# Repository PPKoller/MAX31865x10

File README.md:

# MAX31865x10
PCB for serial 4-point measurement of ten PT-100 temperature sensors using Raspberry Pi.

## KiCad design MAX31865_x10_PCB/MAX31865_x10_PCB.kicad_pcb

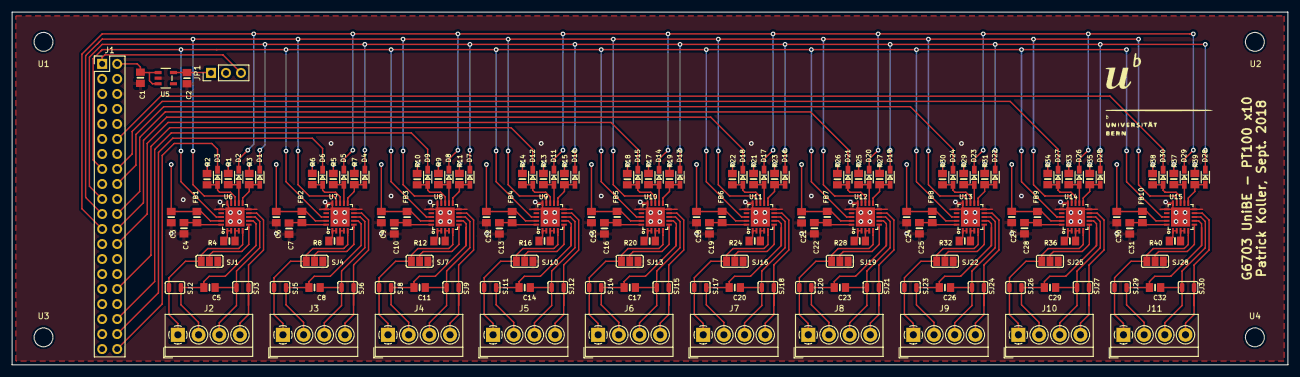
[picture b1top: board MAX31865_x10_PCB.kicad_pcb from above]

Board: 2 copper layers, 215.9 x 59.7 mm, 169 parts (0 on the bottom side), 128 nets.

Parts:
C1, C2: 10uF; 0805-NO
C3, C4, C6, C7, C9, C10, C12, C13, C15, C16, C18, C19, C21, C22, C24, C25, C27, C28, C30, C31: 0.1uF; 0805-NO
C5, C8, C11, C14, C17, C20, C23, C26, C29, C32: 100nF; 0805-NO
D1, D2, D3, D4, D5, D6, D7, D8, D9, D10, D11, D12, D13, D14, D15, D16, D17, D18, D19, D20, D21, D22, D23, D24, D25, D26, D27, D28, D29, D30: 1N4148; SOD-323
FB1, FB2, FB3, FB4, FB5, FB6, FB7, FB8, FB9, FB10: FERRITE-0805NO; 0805-NO
J1: Conn_02x20_Odd_Even; PinHeader_2x20_P2.54mm_Vertical
J2, J3, J4, J5, J6, J7, J8, J9, J10, J11: Conn_01x04; TerminalBlock_4Ucon_1x04_P3.50mm_Horizontal
JP1: Jumper_3_Bridged12; PinHeader_1x03_P2.54mm_Vertical
R1, R2, R3, R5, R6, R7, R9, R10, R11, R13, R14, R15, R17, R18, R19, R21, R22, R23, R25, R26, R27, R29, R30, R31, R33, R34, R35, R37, R38, R39: 10K; 0805-NO
R4, R8, R12, R16, R20, R24, R28, R32, R36, R40: 430Ω / 4300Ω 0.1%; 0805-NO
SJ1, SJ4, SJ7, SJ10, SJ13, SJ16, SJ19, SJ22, SJ25, SJ28: SOLDERJUMPER_2WAY; SOLDERJUMPER_2WAY_OPEN_NOPASTE
SJ2, SJ3, SJ5, SJ6, SJ8, SJ9, SJ11, SJ12, SJ14, SJ15, SJ17, SJ18, SJ20, SJ21, SJ23, SJ24, SJ26, SJ27, SJ29, SJ30: SOLDERJUMPER; SOLDERJUMPER_ARROW_NOPASTE
U1, U2, U3, U4: MOUNTINGHOLE3.0; MountingHole_3.2mm_M3
U5: MIC5225-3.3; SOT23-5
U6, U7, U8, U9, U10, U11, U12, U13, U14, U15: MAX31865; QFN20_4MM_0.65MM

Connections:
CLK_5V: D2.C, D5.C, D8.C, D11.C, D14.C, D17.C, D20.C, D23.C, D26.C, D29.C, J1.23
CS0_5V: D3.C, J1.40
CS1_5V: D6.C, J1.38
CS2_5V: D9.C, J1.36
CS3_5V: D12.C, J1.32
CS4_5V: D15.C, J1.26
CS5_5V: D18.C, J1.24
CS6_5V: D21.C, J1.22
CS7_5V: D24.C, J1.18
CS8_5V: D27.C, J1.16
CS9_5V: D30.C, J1.12
EXT_3V3: J1.1, JP1.3
EXT_5V: C1.1, J1.2, U5.1, U5.3
GND: C1.2, C2.2, C3.2, C4.2, C6.2, C7.2, C9.2, C10.2, C12.2, C13.2, C15.2, C16.2, C18.2, C19.2, C21.2, C22.2, C24.2, C25.2, C27.2, C28.2, C30.2, C31.2, J1.6, SJ1.1, SJ4.1, SJ7.1, SJ10.1, SJ13.1, SJ16.1, SJ19.1, SJ22.1, SJ25.1, SJ28.1, U5.2, U6.10, U6.15, U6.16, U6.PAD, U7.10, U7.15, U7.16, U7.PAD, U8.10, U8.15, U8.16, U8.PAD, U9.10, U9.15, U9.16, U9.PAD, U10.10, U10.15, U10.16, U10.PAD, U11.10, U11.15, U11.16, U11.PAD, U12.10, U12.15, U12.16, U12.PAD, U13.10, U13.15, U13.16, U13.PAD, U14.10, U14.15, U14.16, U14.PAD, U15.10, U15.15, U15.16, U15.PAD
unnamed: C4.1, FB1.1, U6.20
unnamed: C5.1, J2.2, SJ2.1, U6.7
unnamed: C5.2, J2.3, SJ3.2, U6.8
unnamed: C7.1, FB2.1, U7.20
unnamed: C8.1, J3.2, SJ5.1, U7.7
unnamed: C8.2, J3.3, SJ6.2, U7.8
unnamed: C10.1, FB3.1, U8.20
unnamed: C11.1, J4.2, SJ8.1, U8.7
unnamed: C11.2, J4.3, SJ9.2, U8.8
unnamed: C13.1, FB4.1, U9.20
unnamed: C14.1, J5.2, SJ11.1, U9.7
unnamed: C14.2, J5.3, SJ12.2, U9.8
unnamed: C16.1, FB5.1, U10.20
unnamed: C17.1, J6.2, SJ14.1, U10.7
unnamed: C17.2, J6.3, SJ15.2, U10.8
unnamed: C19.1, FB6.1, U11.20
unnamed: C20.1, J7.2, SJ17.1, U11.7
unnamed: C20.2, J7.3, SJ18.2, U11.8
unnamed: C22.1, FB7.1, U12.20
unnamed: C23.1, J8.2, SJ20.1, U12.7
unnamed: C23.2, J8.3, SJ21.2, U12.8
unnamed: C25.1, FB8.1, U13.20
unnamed: C26.1, J9.2, SJ23.1, U13.7
unnamed: C26.2, J9.3, SJ24.2, U13.8
unnamed: C28.1, FB9.1, U14.20
unnamed: C29.1, J10.2, SJ26.1, U14.7
unnamed: C29.2, J10.3, SJ27.2, U14.8
unnamed: C31.1, FB10.1, U15.20
unnamed: C32.1, J11.2, SJ29.1, U15.7
unnamed: C32.2, J11.3, SJ30.2, U15.8
unnamed: D1.A, R3.1, U6.11
unnamed: D2.A, R1.1, U6.12
unnamed: D3.A, R2.1, U6.13
unnamed: D4.A, R7.1, U7.11
unnamed: D5.A, R5.1, U7.12
unnamed: D6.A, R6.1, U7.13
unnamed: D7.A, R11.1, U8.11
unnamed: D8.A, R9.1, U8.12
unnamed: D9.A, R10.1, U8.13
unnamed: D10.A, R15.1, U9.11
unnamed: D11.A, R13.1, U9.12
unnamed: D12.A, R14.1, U9.13
unnamed: D13.A, R19.1, U10.11
unnamed: D14.A, R17.1, U10.12
unnamed: D15.A, R18.1, U10.13
unnamed: D16.A, R23.1, U11.11
unnamed: D17.A, R21.1, U11.12
unnamed: D18.A, R22.1, U11.13
unnamed: D19.A, R27.1, U12.11
unnamed: D20.A, R25.1, U12.12
unnamed: D21.A, R26.1, U12.13
unnamed: D22.A, R31.1, U13.11
unnamed: D23.A, R29.1, U13.12
unnamed: D24.A, R30.1, U13.13
unnamed: D25.A, R35.1, U14.11
unnamed: D26.A, R33.1, U14.12
unnamed: D27.A, R34.1, U14.13
unnamed: D28.A, R39.1, U15.11
unnamed: D29.A, R37.1, U15.12
unnamed: D30.A, R38.1, U15.13
unnamed: J2.1, SJ1.3, SJ2.2, U6.5
unnamed: J2.4, SJ3.1, U6.9
unnamed: J3.1, SJ4.3, SJ5.2, U7.5
unnamed: J3.4, SJ6.1, U7.9
unnamed: J4.1, SJ7.3, SJ8.2, U8.5
unnamed: J4.4, SJ9.1, U8.9
unnamed: J5.1, SJ10.3, SJ11.2, U9.5
unnamed: J5.4, SJ12.1, U9.9
unnamed: J6.1, SJ13.3, SJ14.2, U10.5
unnamed: J6.4, SJ15.1, U10.9
unnamed: J7.1, SJ16.3, SJ17.2, U11.5
unnamed: J7.4, SJ18.1, U11.9
unnamed: J8.1, SJ19.3, SJ20.2, U12.5
unnamed: J8.4, SJ21.1, U12.9
unnamed: J9.1, SJ22.3, SJ23.2, U13.5
unnamed: J9.4, SJ24.1, U13.9
unnamed: J10.1, SJ25.3, SJ26.2, U14.5
unnamed: J10.4, SJ27.1, U14.9
unnamed: J11.1, SJ28.3, SJ29.2, U15.5
unnamed: J11.4, SJ30.1, U15.9
unnamed: R4.1, U6.3, U6.4
unnamed: R4.2, U6.1, U6.2
unnamed: R8.1, U7.3, U7.4
unnamed: R8.2, U7.1, U7.2
unnamed: R12.1, U8.3, U8.4
unnamed: R12.2, U8.1, U8.2
unnamed: R16.1, U9.3, U9.4
unnamed: R16.2, U9.1, U9.2
unnamed: R20.1, U10.3, U10.4
unnamed: R20.2, U10.1, U10.2
unnamed: R24.1, U11.3, U11.4
unnamed: R24.2, U11.1, U11.2
unnamed: R28.1, U12.3, U12.4
unnamed: R28.2, U12.1, U12.2
unnamed: R32.1, U13.3, U13.4
unnamed: R32.2, U13.1, U13.2
unnamed: R36.1, U14.3, U14.4
unnamed: R36.2, U14.1, U14.2
unnamed: R40.1, U15.3, U15.4
unnamed: R40.2, U15.1, U15.2
unnamed: SJ1.2, U6.6
unnamed: SJ4.2, U7.6
unnamed: SJ7.2, U8.6
unnamed: SJ10.2, U9.6
unnamed: SJ13.2, U10.6
unnamed: SJ16.2, U11.6
unnamed: SJ19.2, U12.6
unnamed: SJ22.2, U13.6
unnamed: SJ25.2, U14.6
unnamed: SJ28.2, U15.6
RDY: J1.15, U6.18, U7.18, U8.18, U9.18, U10.18, U11.18, U12.18, U13.18, U14.18, U15.18
SDI_5V: D1.C, D4.C, D7.C, D10.C, D13.C, D16.C, D19.C, D22.C, D25.C, D28.C, J1.19
SDO: J1.21, U6.14, U7.14, U8.14, U9.14, U10.14, U11.14, U12.14, U13.14, U14.14, U15.14
VDD: C2.1, C3.1, C6.1, C9.1, C12.1, C15.1, C18.1, C21.1, C24.1, C27.1, C30.1, FB1.2, FB2.2, FB3.2, FB4.2, FB5.2, FB6.2, FB7.2, FB8.2, FB9.2, FB10.2, JP1.1, JP1.2, R1.2, R2.2, R3.2, R5.2, R6.2, R7.2, R9.2, R10.2, R11.2, R13.2, R14.2, R15.2, R17.2, R18.2, R19.2, R21.2, R22.2, R23.2, R25.2, R26.2, R27.2, R29.2, R30.2, R31.2, R33.2, R34.2, R35.2, R37.2, R38.2, R39.2, U5.5, U6.19, U7.19, U8.19, U9.19, U10.19, U11.19, U12.19, U13.19, U14.19, U15.19

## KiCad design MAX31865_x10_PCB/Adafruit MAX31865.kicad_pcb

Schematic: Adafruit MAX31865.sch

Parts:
C1, C2: 0.1uF; 0805-NO
C3: 100nF; 0805-NO
C4, C5: 10uF; 0805-NO
D1, D2, D3: 1N4148; SOD-323
FB1: FERRITE-0805NO; 0805-NO
FID1, FID2: FIDUCIAL\"\"; FIDUCIAL_1MM
JP1: HEADER-1X870MIL; 1X08_ROUND_70
R1: 430Ω / 4300Ω 0.1%; 0805-NO
R6, R7, R8: 10K; 0805-NO
SJ1: SOLDERJUMPER_2WAY; SOLDERJUMPER_2WAY_OPEN_NOPASTE
SJ3, SJ4: SOLDERJUMPER; SOLDERJUMPER_ARROW_NOPASTE
U1: MAX31865; QFN20_4MM_0.65MM
U3: MIC5225-3.3; SOT23-5
U$18, U$19: MOUNTINGHOLE2.5; MOUNTINGHOLE_2.5_PLATED
X1, X2: 3.5mm; TERMBLOCK_1X2-3.5MM

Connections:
/CS_5V: D3.C, JP1.7
/DRDY: JP1.8, U1.18 (DRDY)
/SCLK_5V: D2.C, JP1.4
/SDI_5V: D1.C, JP1.6
/SDO: JP1.5, U1.14 (SDO)
GND: C1.2, C2.2, C4.2, C5.2, JP1.2, SJ1.1, U1.10 (AGND@2), U1.15 (GND), U1.16 (ANGD@1), U1.PAD, U3.2 (GND)
unnamed: C2.1, FB1.1, U1.20 (VDD)
unnamed: C3.1, SJ3.1, U1.7 (RTDIN+), X1.1
unnamed: C3.2, SJ4.2, U1.8 (RTDIN-), X2.2
unnamed: D1.A, R6.1, U1.11 (SDI)
unnamed: D2.A, R8.1, U1.12 (SCLK)
unnamed: D3.A, R7.1, U1.13 (CS)
unnamed: R1.1, U1.3 (REFIN-), U1.4 (ISENSOR)
unnamed: R1.2, U1.1 (BIAS), U1.2 (REFIN+)
unnamed: SJ1.2, U1.6 (FORCE2)
unnamed: SJ1.3, SJ3.2, U1.5 (FORCE+), X1.2
unnamed: SJ4.1, U1.9 (FORCE-), X2.1
VDD: C1.1, C5.1, FB1.2, JP1.3, R6.2, R7.2, R8.2, U1.19 (DVDD), U3.5 (OUT)
VIN: C4.1, JP1.1, U3.1 (IN), U3.3 (EN)

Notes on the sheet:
C3 = 100nF for 100 ohm RTD, 10nF for 1K
R1 = 4x RTD resistance at 0°C (so 400 ohm for a 100 ohm RTD). Use high quality 1% or better resistors
SJ1 to GND for 2/4-wire, to FORCE+ for 3-wire
SJ2 closed on 2/3-wire setups, open for 4-wire

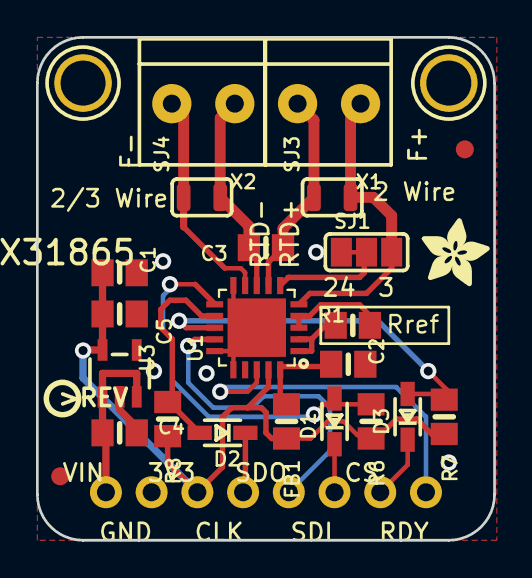
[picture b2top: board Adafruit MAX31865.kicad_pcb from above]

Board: 2 copper layers, 25.4 x 27.9 mm, 29 parts (0 on the bottom side), 19 nets.

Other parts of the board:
U$8: PCBFEAT-REV-040
U$16: ADAFRUIT_3.5MM
U$20, U$21: ADAFRUIT_5MM

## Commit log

2020-02-25 Patrick: first commit.
